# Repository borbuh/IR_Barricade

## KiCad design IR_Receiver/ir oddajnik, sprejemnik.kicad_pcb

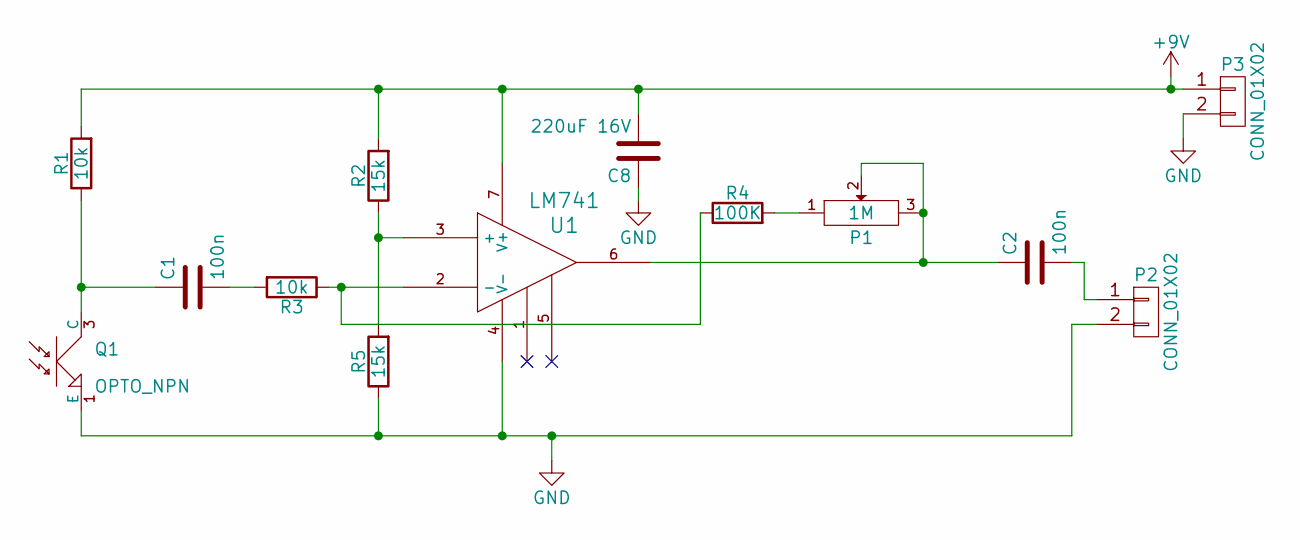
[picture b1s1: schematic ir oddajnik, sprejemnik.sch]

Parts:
C1, C2: 100n; C_Disc_D4.7mm_W2.5mm_P5.00mm
C8: 220uF 16V; CP_Radial_D8.0mm_P3.80mm
P1: 1M; Potentiometer_Trimmer_ACP_CA9v_Horizontal_Px10.0mm_Py5.0mm
P2, P3: CONN_01X02; TerminalBlock_bornier-2_P5.08mm
Q1: OPTO_NPN; OPIC_Sharp_IS485
R1, R3: 10k; R_Axial_DIN0207_L6.3mm_D2.5mm_P7.62mm_Horizontal
R2, R5: 15k; R_Axial_DIN0207_L6.3mm_D2.5mm_P7.62mm_Horizontal
R4: 100K; R_Axial_DIN0207_L6.3mm_D2.5mm_P7.62mm_Horizontal
U1: LM741; PDIP-8

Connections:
+9V: C8.2, P3.1, R1.2, R2.2, U1.7 (V+)
GND: C8.1, P2.2, P3.2, Q1.1 (E), R5.1, U1.4 (V-)
unnamed: C1.1, Q1.3 (C), R1.1
unnamed: C1.2, R3.2
unnamed: C2.1, P1.2, P1.3, U1.6
unnamed: C2.2, P2.1
unnamed: P1.1, R4.2
unnamed: R2.1, R5.2, U1.3 (+)
unnamed: R3.1, R4.1, U1.2 (-)

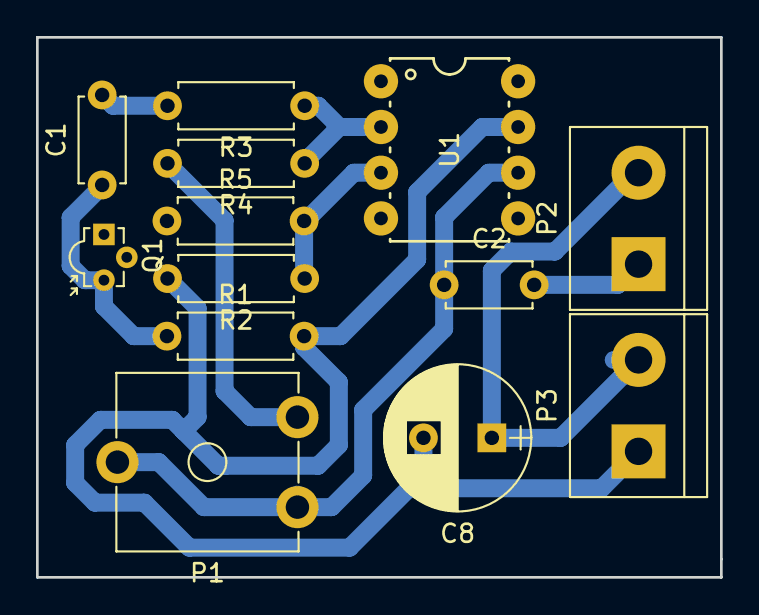
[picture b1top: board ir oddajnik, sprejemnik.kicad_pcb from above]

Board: 2 copper layers, 38.0 x 30.0 mm, 13 parts (0 on the bottom side), 9 nets.

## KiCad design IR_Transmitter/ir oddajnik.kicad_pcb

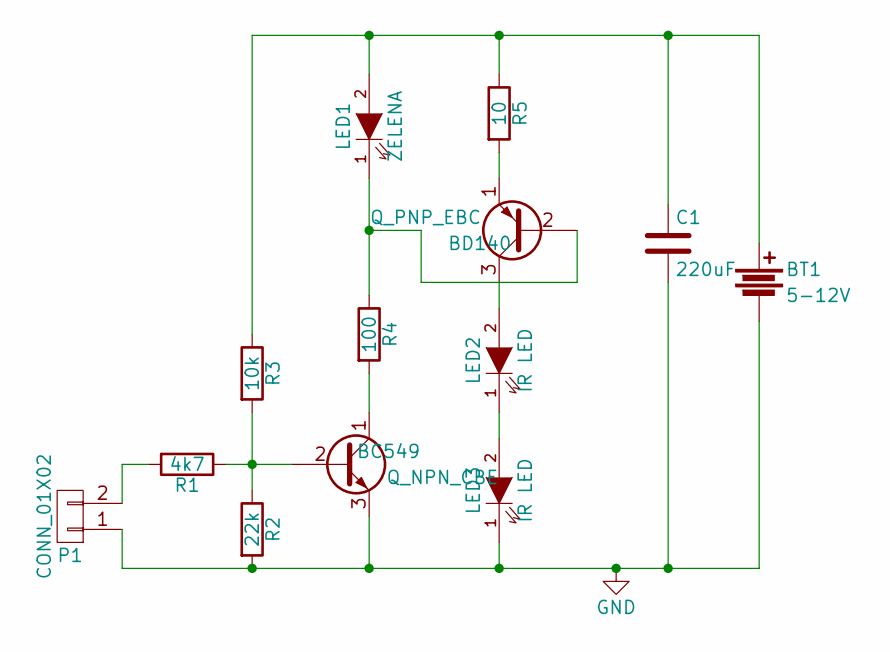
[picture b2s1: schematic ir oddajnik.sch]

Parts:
BC549: Q_NPN_CBE; TO-92_Inline_Wide
BD140: Q_PNP_EBC; TO-92_Inline_Wide
BT1: 5-12V; TerminalBlock_bornier-2_P5.08mm
C1: 220uF; CP_Radial_D8.0mm_P3.80mm
LED1: ZELENA; LED_D5.0mm
LED2, LED3: IR LED; LED_D5.0mm
P1: CONN_01X02; TerminalBlock_bornier-2_P5.08mm
R1: 4k7; R_Axial_DIN0204_L3.6mm_D1.6mm_P7.62mm_Horizontal
R2: 22k; R_Axial_DIN0204_L3.6mm_D1.6mm_P7.62mm_Horizontal
R3: 10k; R_Axial_DIN0204_L3.6mm_D1.6mm_P7.62mm_Horizontal
R4: 100; R_Axial_DIN0204_L3.6mm_D1.6mm_P7.62mm_Horizontal
R5: 10; R_Axial_DIN0204_L3.6mm_D1.6mm_P7.62mm_Horizontal

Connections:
GND: BC549.3 (E), BT1.2, C1.2, LED3.1 (K), P1.1, R2.2
unnamed: BC549.1 (C), R4.2
unnamed: BC549.2 (B), R1.1, R2.1, R3.2
unnamed: BD140.1 (E), R5.2
unnamed: BD140.2 (B), LED1.1 (K), R4.1
unnamed: BD140.3 (C), LED2.2 (A)
unnamed: BT1.1, C1.1, LED1.2 (A), R3.1, R5.1
unnamed: LED2.1 (K), LED3.2 (A)
unnamed: P1.2, R1.2

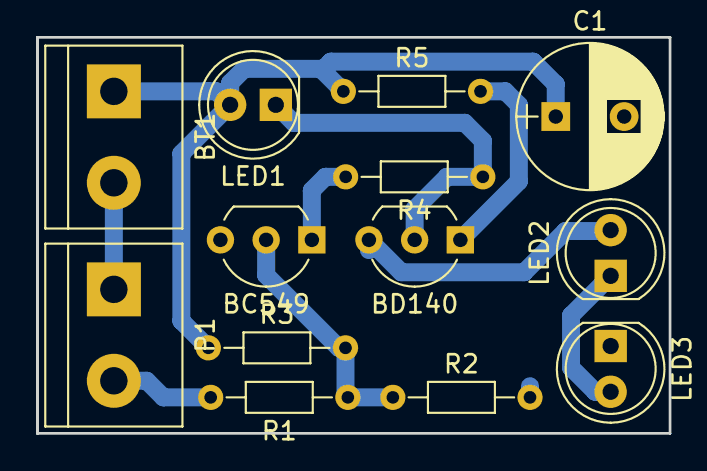
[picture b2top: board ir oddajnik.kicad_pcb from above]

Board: 2 copper layers, 35.2 x 22.0 mm, 13 parts (0 on the bottom side), 9 nets.
